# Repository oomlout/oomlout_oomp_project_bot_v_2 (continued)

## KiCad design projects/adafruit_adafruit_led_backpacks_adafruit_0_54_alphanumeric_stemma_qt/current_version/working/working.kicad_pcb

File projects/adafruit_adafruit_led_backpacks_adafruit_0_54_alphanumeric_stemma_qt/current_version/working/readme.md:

# adafruit_led_backpacks
 
## summary 
* id: adafruit_adafruit_led_backpacks_adafruit_0_54_alphanumeric_stemma_qt
* user: adafruit
* name: adafruit_led_backpacks
* board: adafruit_0_54_alphanumeric_stemma_qt
* repo: https://github.com/adafruit/Adafruit-LED-Backpacks

* src_file_repo_sch: 
* src_file_repo_sch_link: https://github.com/adafruit/Adafruit-LED-Backpacks/tree/master/
* full details link: https://github.com/oomlout/oomlout_oomp_project_bot_v_2/tree/main/projects/adafruit_adafruit_led_backpacks_adafruit_0_54_alphanumeric_stemma_qt/current_version/working  

## schematic  
  
[schematic (pdf)](working_schematic.pdf) 

## pcb  

[board (pdf)](working.pdf)  

## working_bom
| Id | Designator | Footprint | Quantity | Designation | Supplier and ref |  | None | 
| --- | --- | --- | --- | --- | --- | --- | --- | 
| 1 | @HOLE3,@HOLE2,@HOLE1,@HOLE0 |  | 4 |  |  |  | [''] | 
| 2 | R1,R2 | 0603-NO | 2 | 10K |  |  | [''] | 
| 3 | CONN2,CONN1 | JST_SH4_RA | 2 | STEMMA_I2C_QTRA |  |  | [''] | 
| 4 | A0,A1,A2 | SOLDERJUMPER_REFLOW_NOPASTE | 3 |  |  |  | [''] | 
| 5 | D3,D1 | SOD-323F | 2 | CUS530 |  |  | [''] | 
| 6 | C1 | 0805-NO | 1 | 10uF |  |  | [''] | 
| 7 | R5,R6,R3,R4 | 0603-NO | 4 | 47K |  |  | [''] | 
| 8 | U$3 | ADAFRUIT_5MM | 1 |  |  |  | [''] | 
| 9 | D2 | CHIPLED_0603_NOOUTLINE | 1 | GREEN |  |  | [''] | 
| 10 | U$2,U$1 | FIDUCIAL_1MM | 2 | FIDUCIAL |  |  | [''] | 
| 11 | U2 | SOP28_300MIL_SKINNY | 1 | HT16K33 |  |  | [''] | 
| 12 | JP1 | 1X05_ROUND_70 | 1 |  |  |  | [''] | 
| 13 | U$7,U$6 | STEMMAQT | 2 |  |  |  | [''] | 
| 14 | U$8 | PCBFEAT-REV-040 | 1 |  |  |  | [''] | 
| 15 | LEDJMP0 | SOLDERJUMPER_CLOSEDWIRE | 1 |  |  |  | [''] | 
| 16 | LED1,LED2 | SEGMENT_STARTBUST_DUAL_KWA-541CBB | 2 |  |  |  | [''] | 

## bom_schematic
| Ref | Qnty | Value | Cmp name | Footprint | Description | Vendor | DNP | 
| --- | --- | --- | --- | --- | --- | --- | --- | 
| A0, A1, A2 | 3 | SOLDERJUMPERREFLOW_NOPASTE | SOLDERJUMPERREFLOW_NOPASTE | working:SOLDERJUMPER_REFLOW_NOPASTE |  |  |  | 
| C1 | 1 | 10uF | CAP_CERAMIC0805-NOOUTLINE | working:0805-NO |  |  |  | 
| CONN1, CONN2 | 2 | STEMMA_I2C_QTRA | STEMMA_I2C_QTRA | working:JST_SH4_RA |  |  |  | 
| D1, D3 | 2 | CUS530 | DIODESOD-323F | working:SOD-323F |  |  |  | 
| D2 | 1 | GREEN | LED0603_NOOUTLINE | working:CHIPLED_0603_NOOUTLINE |  |  |  | 
| JP1 | 1 | HEADER-1X570MIL | HEADER-1X570MIL | working:1X05_ROUND_70 |  |  |  | 
| LED1, LED2 | 2 | DISP_SEGMENT_STARBURST_DUAL_COMMONCATHODE | DISP_SEGMENT_STARBURST_DUAL_COMMONCATHODE | working:SEGMENT_STARTBUST_DUAL_KWA-541CBB |  |  |  | 
| LEDJMP0 | 1 | SOLDERJUMPERCLOSED | SOLDERJUMPERCLOSED | working:SOLDERJUMPER_CLOSEDWIRE |  |  |  | 
| R1, R2 | 2 | 10K | RESISTOR_0603_NOOUT | working:0603-NO |  |  |  | 
| R3, R4, R5, R6 | 4 | 47K | RESISTOR_0603_NOOUT | working:0603-NO |  |  |  | 
| U2 | 1 | HT16K33 | HT16K33_SOP28_SKINNY | working:SOP28_300MIL_SKINNY |  |  |  | 
| U$1, U$2 | 2 | FIDUCIAL | FIDUCIAL | working:FIDUCIAL_1MM |  |  |  |

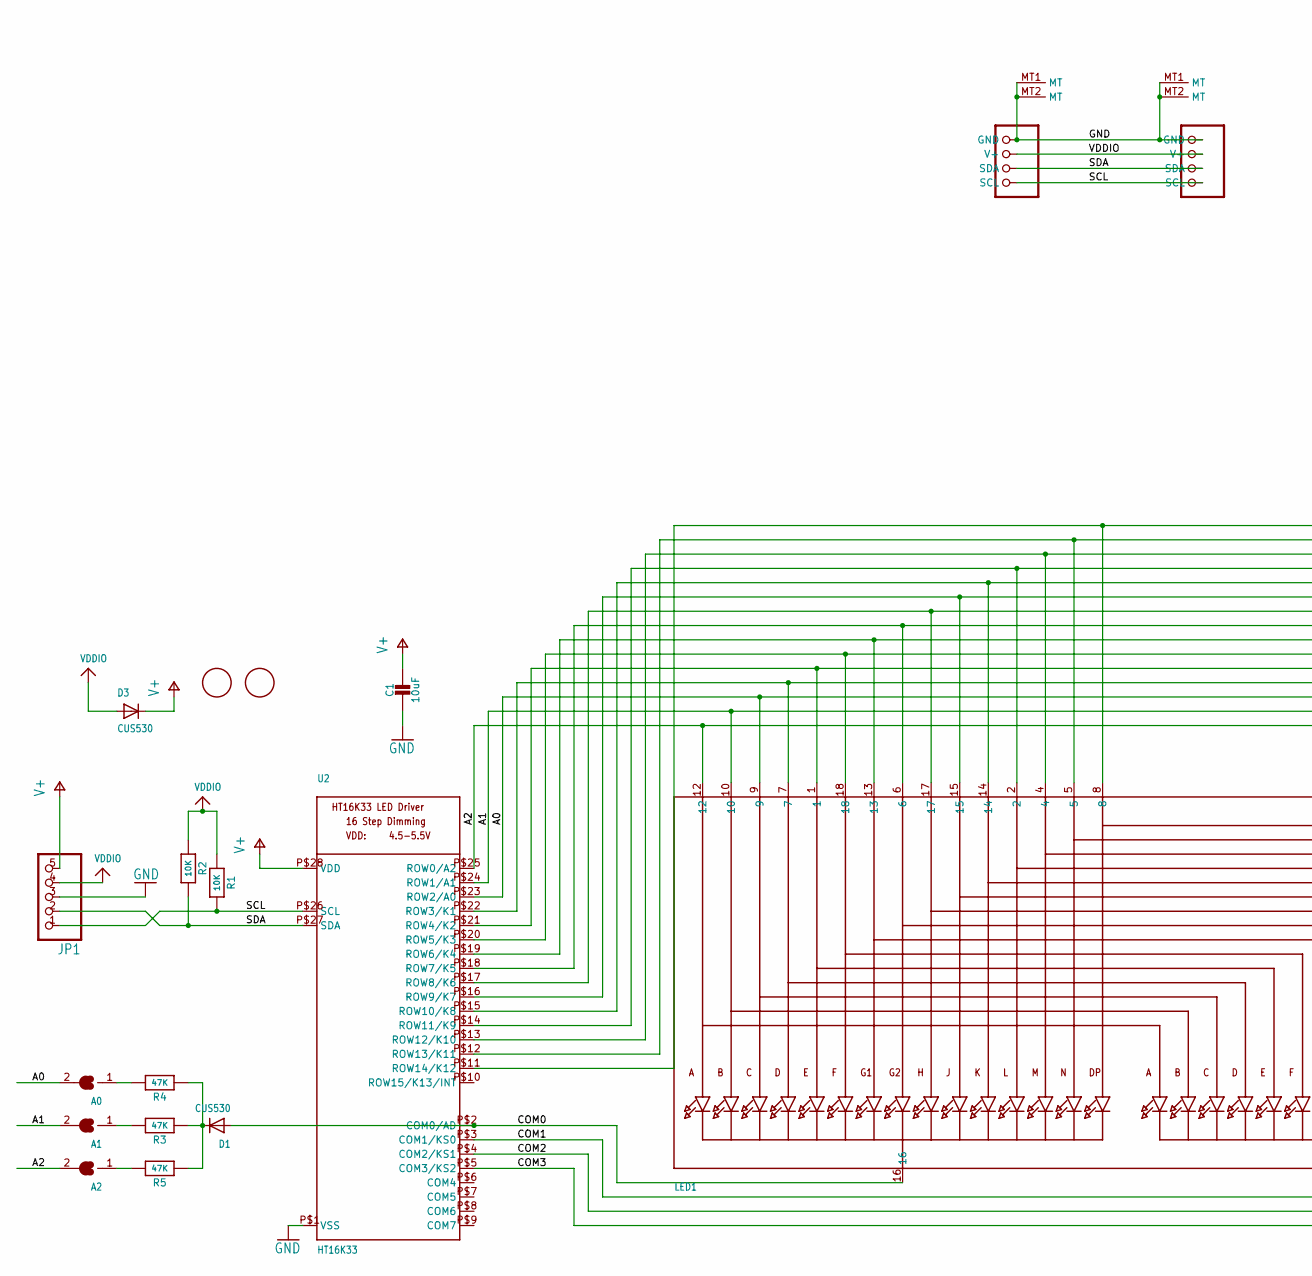
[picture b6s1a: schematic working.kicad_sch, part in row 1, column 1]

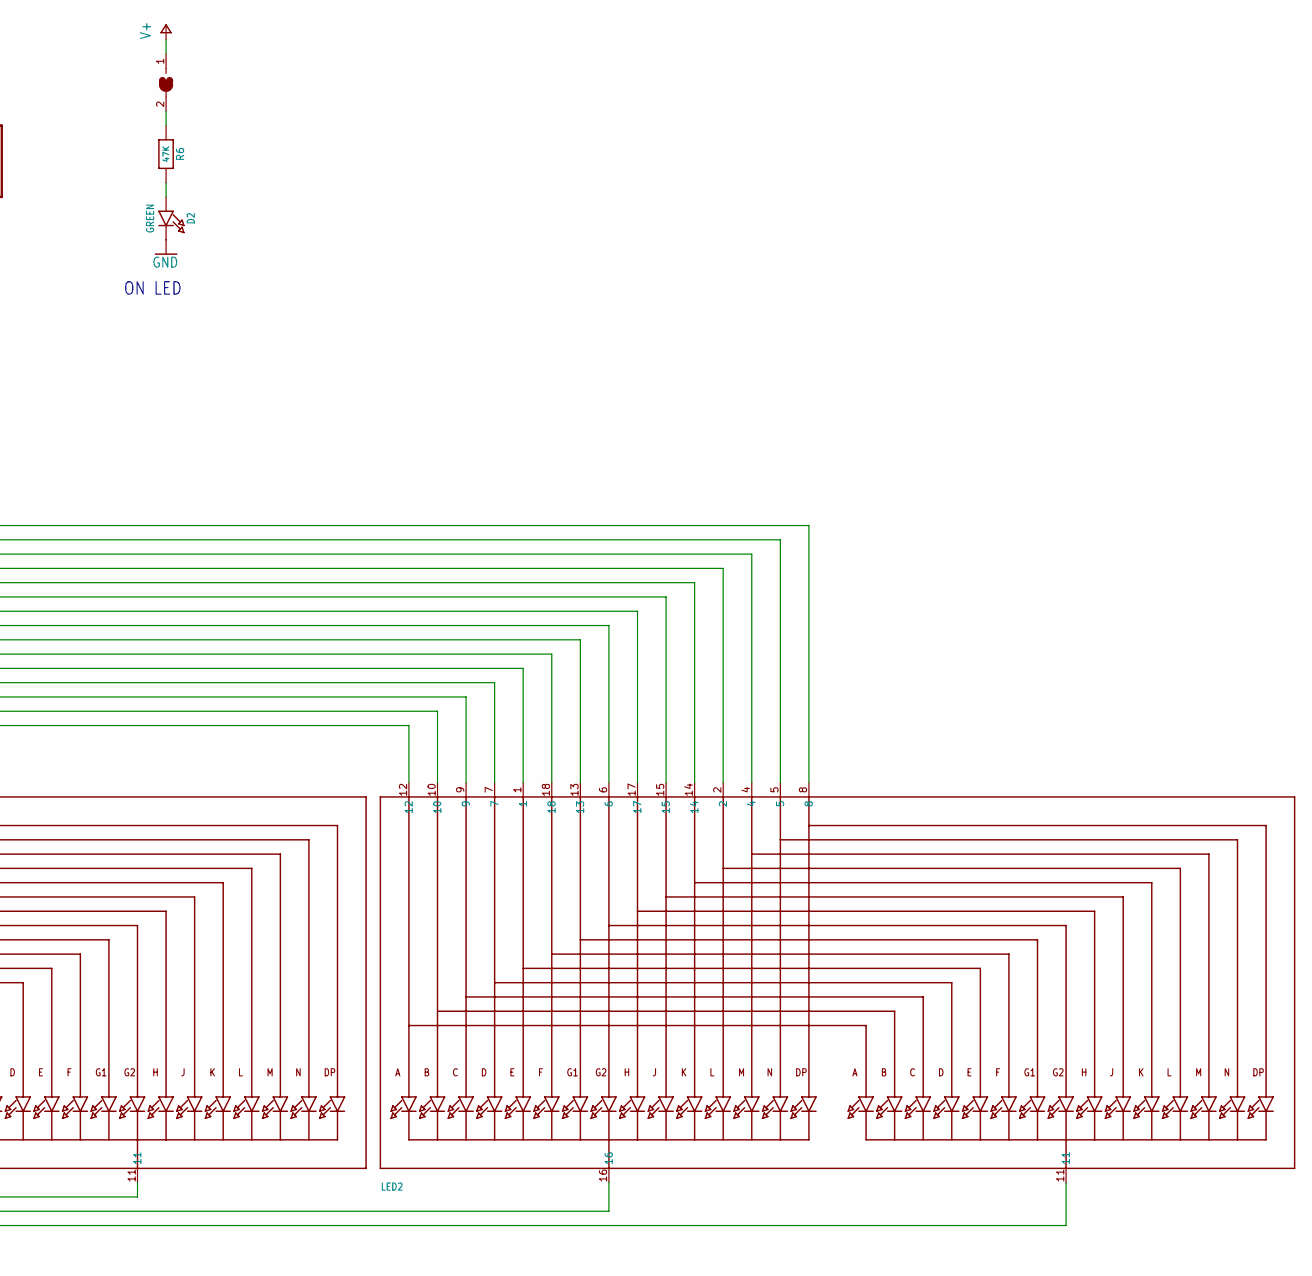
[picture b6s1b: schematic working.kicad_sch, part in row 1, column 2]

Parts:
A0, A1, A2: SOLDERJUMPERREFLOW_NOPASTE; SOLDERJUMPER_REFLOW_NOPASTE
C1: 10uF; 0805-NO
CONN1, CONN2: STEMMA_I2C_QTRA; JST_SH4_RA
D1, D3: CUS530; SOD-323F
D2: GREEN; CHIPLED_0603_NOOUTLINE
JP1: HEADER-1X570MIL; 1X05_ROUND_70
LED1, LED2: DISP_SEGMENT_STARBURST_DUAL_COMMONCATHODE; SEGMENT_STARTBUST_DUAL_KWA-541CBB
LEDJMP0: SOLDERJUMPERCLOSED; SOLDERJUMPER_CLOSEDWIRE
R1, R2: 10K; 0603-NO
R3, R4, R5, R6: 47K; 0603-NO
U2: HT16K33; SOP28_300MIL_SKINNY
U$1, U$2: FIDUCIAL; FIDUCIAL_1MM

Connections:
A0: A0.2, LED1.9, LED2.9, U2.P$23 (ROW2/A0)
A1: A1.2, LED1.10, LED2.10, U2.P$24 (ROW1/A1)
A2: A2.2, LED1.12, LED2.12, U2.P$25 (ROW0/A2)
COM0: D1.A, LED1.16, U2.P$2 (COM0/AD)
COM1: LED1.11, U2.P$3 (COM1/KS0)
COM2: LED2.16, U2.P$4 (COM2/KS1)
COM3: LED2.11, U2.P$5 (COM3/KS2)
GND: C1.2, CONN1.1 (GND), CONN1.MT1 (MT), CONN1.MT2 (MT), CONN2.1 (GND), CONN2.MT1 (MT), CONN2.MT2 (MT), D2.C, JP1.3, U2.P$1 (VSS)
unnamed: D1.C, R3.1, R4.1, R5.1
unnamed: D2.A, R6.2
unnamed: LED1.17, LED2.17, U2.P$17 (ROW8/K6)
unnamed: LED1.15, LED2.15, U2.P$16 (ROW9/K7)
unnamed: LED1.14, LED2.14, U2.P$15 (ROW10/K8)
unnamed: A2.1, R5.2
unnamed: LED1.2, LED2.2, U2.P$14 (ROW11/K9)
unnamed: LED1.4, LED2.4, U2.P$13 (ROW12/K10)
unnamed: LED1.7, LED2.7, U2.P$22 (ROW3/K1)
unnamed: LED1.1, LED2.1, U2.P$21 (ROW4/K2)
unnamed: LED1.18, LED2.18, U2.P$20 (ROW5/K3)
unnamed: LED1.13, LED2.13, U2.P$19 (ROW6/K4)
unnamed: LED1.5, LED2.5, U2.P$12 (ROW13/K11)
unnamed: LED1.8, LED2.8, U2.P$11 (ROW14/K12)
unnamed: LED1.6, LED2.6, U2.P$18 (ROW7/K5)
unnamed: LEDJMP0.2, R6.1
unnamed: A1.1, R3.2
unnamed: A0.1, R4.2
SCL: CONN1.4 (SCL), CONN2.4 (SCL), JP1.1, R1.2, U2.P$26 (SCL)
SDA: CONN1.3 (SDA), CONN2.3 (SDA), JP1.2, R2.2, U2.P$27 (SDA)
V+: C1.1, D3.C, JP1.5, LEDJMP0.1, U2.P$28 (VDD)
VDDIO: CONN1.2 (V+), CONN2.2 (V+), D3.A, JP1.4, R1.1, R2.1

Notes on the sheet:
ON LED

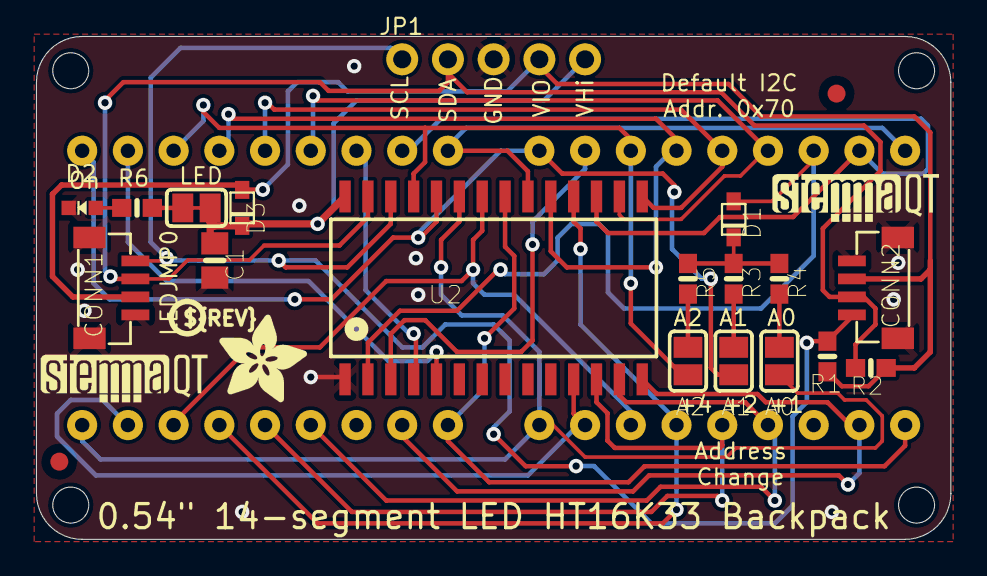
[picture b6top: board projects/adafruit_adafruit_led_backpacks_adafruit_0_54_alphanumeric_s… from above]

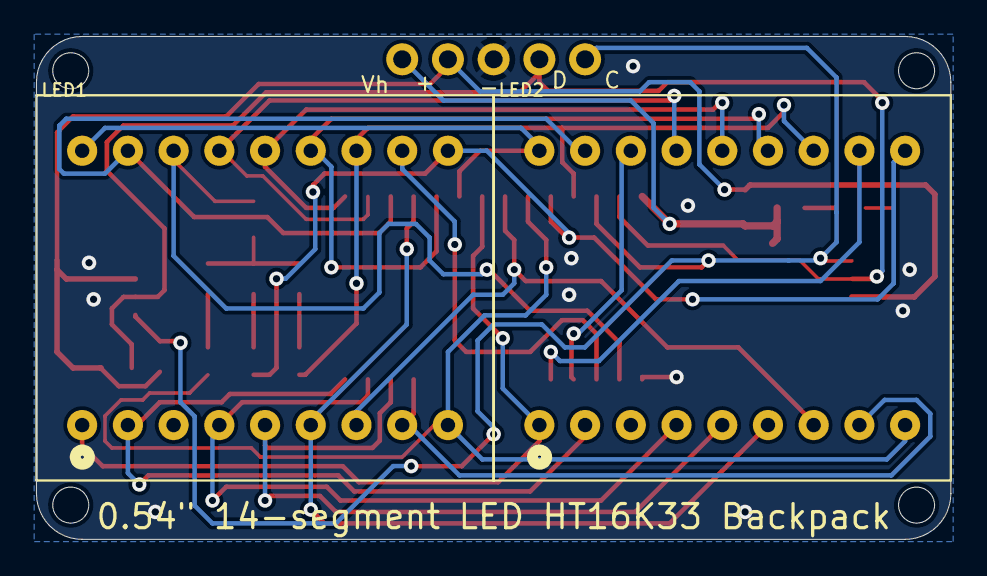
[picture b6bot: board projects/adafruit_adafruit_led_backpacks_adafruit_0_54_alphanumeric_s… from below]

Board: 16 copper layers, 50.8 x 27.9 mm, 30 parts (2 on the bottom side), 30 nets.

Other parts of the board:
@HOLE0, @HOLE1, @HOLE2, @HOLE3: (no value)
U$3: ADAFRUIT_5MM
U$6, U$7: STEMMAQT
U$8: PCBFEAT-REV-040
